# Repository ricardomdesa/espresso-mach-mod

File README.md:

# ☕ ESPresso

**Cafeteira Philco Espresso turbinada com um ESP32-C3:** controle PID de
temperatura da caldeira, modo vaporização, provisionamento Wi-Fi, API
REST/WebSocket e um app mobile (React + Capacitor) para configurar tudo.
Acompanha um **simulador em Go** que emula o firmware inteiro — dá pra
desenvolver o app sem encostar no hardware.

> ⚠️ **Projeto de hobby, mexe com rede elétrica AC.** SSR de 25 A, bomba
> vibratória e resistência de caldeira ligados na tomada. Se você não sabe
> isolar o lado AC do lado DC com segurança, **não reproduza.** Sem garantia
> de nada.

---

## O que dá pra fazer

- **PID de temperatura** na caldeira via SSR (time-proportioning, janela de 1 s),
  com anti-windup, derivada sobre a medição e cadência de 200 ms.
- **Termopar tipo K real** (MAX6675, SPI) com calibração linear de offset/ganho.
- **Modo vaporização:** o PID passa a mirar um alvo de vapor editável
  (80–115 °C) sem gravar na NVS; ao desligar, o setpoint de café volta para 70 °C.
- **Relé "temperatura pronta"** (contato seco, com histerese) para puxar shot
  manualmente, sem depender do app.
- **Perfis de extração** (pré-infusão, rampa, declínio) com CRUD pelo app e
  persistência em NVS.
- **Provisionamento Wi-Fi** no padrão AP + STA — o AP `Philco-Setup` **nunca**
  abre sozinho, só com hold de 5 s no botão. Descoberta por mDNS (`philco.local`).
- **App mobile** (Android/iOS via Capacitor): dashboard ao vivo por WebSocket,
  ajuste de PID/setpoint, gráficos da extração, histórico local offline.
- **Simulador** que espelha byte a byte o contrato REST/WS do firmware, com
  modelo térmico + PID portados do C++, e uma tela web mostrando SSR, bomba e LEDs.

### Failsafes de segurança

| Camada | Ação |
|---|---|
| Teto de sobretemperatura (115 °C) | duty forçado a 0 %, independente do PID |
| Leitura do termopar parada > 10 s | duty forçado a 0 % (sensor aberto/congelado) |
| Modo AP no ar | aquecedor forçado desligado (o scan de Wi-Fi bloqueia o loop) |
| Fusível na linha AC | última camada, contra SSR travado ligado |

---

## Estrutura do repositório

```
.
├── src/ · include/ · platformio.ini   Firmware ESP32-C3 (Arduino / PlatformIO)
├── secrets.ini.example                Modelo do secrets.ini (código de pareamento)
├── app/                               App React + TypeScript + Vite + Capacitor
├── simulator/                         Servidor Go que emula o ESP32 (REST + WS + web)
├── docs/                              Arquitetura, épicos, SDDs, calibração do PID
└── pinout2-1500.png                   Diagrama de pinagem
```

O firmware é dividido em módulos: `sensors/` (termopar, calibração, fakes),
`control/` (PID, saída do aquecedor), `net/` (Wi-Fi provisioner, servidor da API),
`config/` (NVS), `input/` (botão), `model/` (modelo de dados compartilhado).

---

## Hardware

| Bloco | Peça |
|---|---|
| MCU | ESP32-C3 Super Mini |
| Temperatura | Termopar tipo K + módulo MAX6675 (SPI) |
| Aquecimento | SSR AC 25 A acionado por driver TIP120, resistência original da caldeira |
| Bomba | Bomba vibratória Ulka original + módulo de relé (liga/desliga) |
| Sinalização | LED de iluminação + LED azul onboard |

### Pinagem (ESP32-C3)

| GPIO | Função |
|---|---|
| `3` | Botão tátil — clique: liga/desliga LED de luz · hold 5 s: sobe o AP de config |
| `20` | LED de iluminação (ativo HIGH) |
| `8` | LED azul onboard — pisca em modo setup (ativo LOW) |
| `5` / `6` / `7` | MAX6675 — SCK / SO(MISO) / CS |
| `10` | Base do driver TIP120 do SSR de aquecimento (ativo HIGH) |
| `0` | Sinal do relé da bomba (módulo active-low) |
| `1` | Sinal do relé "temperatura pronta" (contato seco, active-low) |

Detalhes de cada pino (motivo da escolha, strapping pins, estágio driver do SSR)
estão comentados em [`include/pinos.h`](include/pinos.h). Diagrama completo em
[`pinout2-1500.png`](pinout2-1500.png).

---

## Como rodar

### Firmware

Precisa de [PlatformIO](https://platformio.org/).

**Antes do primeiro build**, crie o `secrets.ini` com o código de pareamento da
sua máquina. Ele não é versionado — quem tem o código comanda a máquina (bomba,
setpoint, extração), então não pode viver num repositório público:

```sh
cp secrets.ini.example secrets.ini
openssl rand -hex 6                        # gere um código e ponha em auth_key
```

Sem esse arquivo o build falha de propósito. Anote o código numa etiqueta na
máquina: é ele que o app pede uma vez, no pareamento. Ele também sai no Serial
no boot. Trocar o código exige regravar o firmware e parear o app de novo.

```sh
pio run                                    # compila (env: esp32-c3-super-mini)
pio run -t upload && pio device monitor    # grava e abre o monitor serial (115200)
```

Sem credencial de Wi-Fi salva a máquina fica **offline** e o controle de
temperatura funciona standalone. Hold de 5 s no botão sobe o AP `Philco-Setup`
(IP `192.168.4.1`) para o app fazer o provisionamento.

Ambientes extras de bancada: `pio run -e wifi-ap-test`, `pio run -e wifi-sta-test`.

### App

Precisa de Node.js 18+.

```sh
cd app
npm install
npm run dev                # dev server no browser

npm run build              # build de produção
npx cap sync android       # sincroniza com o projeto nativo
npx cap open android       # abre no Android Studio (idem ios)
```

O app acha a máquina por mDNS (`philco.local`) com fallback para varredura de
subnet, ou por endereço manual (`host:porta`). Histórico de extrações fica local
via `@capacitor/preferences`.

### Simulador

Precisa de Go 1.21+ ou Docker.

```sh
cd simulator
docker compose up --build          # http://localhost:8080  (tela web em /)
# ou:
go run .                           # go run . -port 9000 -no-auth
```

No emulador Android, aponte o app para `10.0.2.2:8080` (endereço manual — a
auto-descoberta não alcança o host). Detalhes e todos os endpoints `/sim/*` de
controle da simulação em [`simulator/README.md`](simulator/README.md).

---

## API

`GET /ws` faz o streaming de leituras a cada 100 ms e emite eventos
(`extraction_started`, `extraction_stopped`, `error`). Rotas que mudam estado
exigem o header `X-Auth-Token` com o código de pareamento (dispensado só no
`provision` em modo AP); CORS liberado, `OPTIONS` responde 204. As rotas de
leitura são públicas: dá para ver as leituras sem código, mas não comandar.

| Método | Rota | O quê |
|---|---|---|
| `GET` | `/api/status` | snapshot completo (temp, pressão, setpoints, PID, flags, IP) |
| `GET` | `/api/auth/check` | valida o código de pareamento — 204 se vale, 401 se não |
| `PUT` | `/api/setpoint/temp` · `/api/setpoint/pressure` | alvos de temperatura / pressão |
| `PUT` | `/api/pid` | ganhos `{kp, ki, kd}` |
| `PUT` | `/api/led` · `/api/pump` · `/api/steam` | LED, bomba, modo vaporização |
| `POST` | `/api/extraction/start` · `/api/extraction/stop` | ciclo de extração + cronômetro |
| `GET` `POST` | `/api/profiles` | listar / criar perfil |
| `PUT` `DELETE` | `/api/profiles/{id}` | editar / remover perfil |
| `PUT` | `/api/profiles/active` | define o perfil ativo `{id}` |
| `GET` | `/api/wifi/scan` | redes visíveis (só em modo AP) |
| `POST` | `/api/wifi/provision` · `/api/wifi/forget` | salvar / esquecer credencial |
| `POST` | `/api/factory-reset` | limpa a NVS |

Contrato completo em [`src/net/ApiServer.cpp`](src/net/ApiServer.cpp) e
[`docs/sdd/006-api-rest-websocket.md`](docs/sdd/006-api-rest-websocket.md).

---

## Documentação

| Arquivo | Conteúdo |
|---|---|
| [`ARCHITECTURE.md`](ARCHITECTURE.md) | visão geral, BOM, divisão de responsabilidades, fluxo de provisionamento |
| [`docs/EPICS.md`](docs/EPICS.md) | roadmap por épicos, cada um com um SDD |
| [`docs/sdd/`](docs/sdd/) | design docs: OLED, sensor, PID, integração, Wi-Fi, API, app |
| [`docs/pid-calibracao.md`](docs/pid-calibracao.md) | log e método da calibração de Kp/Ki/Kd em bancada |

### Roadmap

| # | Épico | Status |
|---|---|---|
| 1 | Scaffold + modelo de dados + botão + cronômetro | ✅ |
| 2 | Sensor de temperatura (MAX6675 + calibração) | ✅ |
| 3 | Controle PID de temperatura + SSR | ✅ |
| 4 | Integração MVP + calibração no hardware | 🔧 em bancada |
| 5 | Wi-Fi + provisionamento (AP/STA, mDNS) | ✅ |
| 6 | API REST/WebSocket + persistência NVS | ✅ |
| 7 | App Android (React + Capacitor) | ✅ |
| — | Sensor de pressão real, balança (dose:yield), OTA | 📋 futuro |

O sensor de pressão ainda é `SensorFake` — o hardware é Fase 2. O OLED local foi
removido do projeto (queimou); toda a UI vive no app.

---

## Licença

A definir. Enquanto isso: use por sua conta e risco, sem garantia.

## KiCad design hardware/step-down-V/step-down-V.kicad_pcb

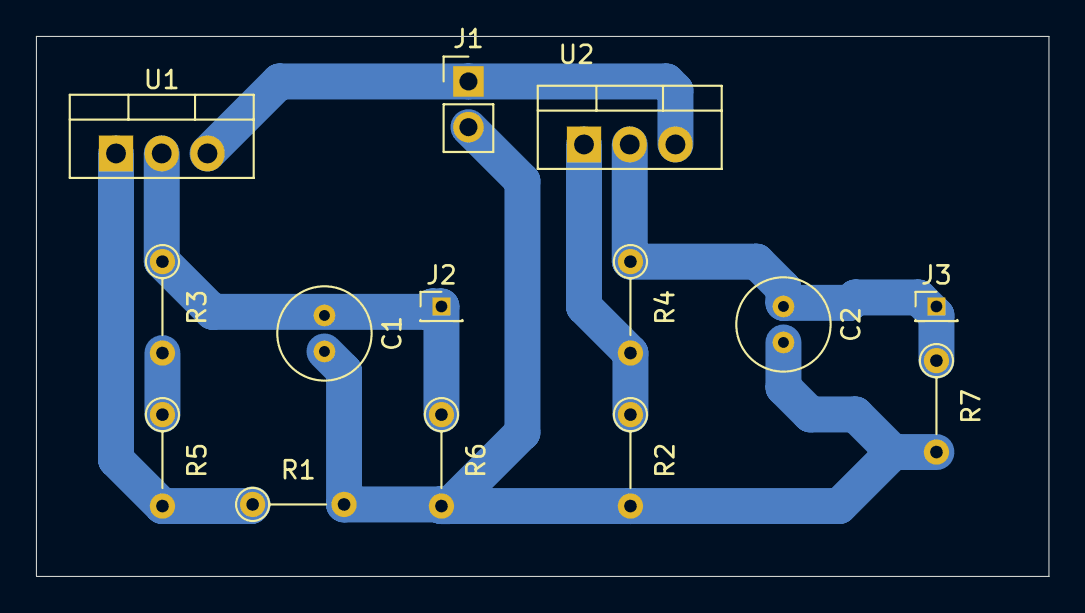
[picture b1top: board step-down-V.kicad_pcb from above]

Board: 2 copper layers, 56.2 x 30.0 mm, 14 parts (0 on the bottom side), 7 nets.

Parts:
C1, C2: C_Polarized; C_Radial_D5.0mm_H5.0mm_P2.00mm
J1: Vin 12V; PinHeader_1x02_P2.54mm_Vertical
J2, J3: Conn_01x01_Socket; PinHeader_1x01_P1.27mm_Vertical
R1: 470; R_Axial_DIN0204_L3.6mm_D1.6mm_P5.08mm_Vertical
R2: 330; R_Axial_DIN0204_L3.6mm_D1.6mm_P5.08mm_Vertical
R3: 120; R_Axial_DIN0204_L3.6mm_D1.6mm_P5.08mm_Vertical
R4: 260; R_Axial_DIN0204_L3.6mm_D1.6mm_P5.08mm_Vertical
R5: 20; R_Axial_DIN0204_L3.6mm_D1.6mm_P5.08mm_Vertical
R6, R7: 1K; R_Axial_DIN0204_L3.6mm_D1.6mm_P5.08mm_Vertical
U1, U2: LM317_TO-220; TO-220-3_Vertical

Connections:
GND: C1.2, C2.2, J1.2, R1.2, R2.2, R6.2, R7.2
unnamed: J1.1, U1.3 (VI), U2.3 (VI)
unnamed: C1.1, J2.1 (Pin_1_1), R3.1, R6.1, U1.2 (VO)
unnamed: C2.1, J3.1 (Pin_1_1), R4.1, R7.1, U2.2 (VO)
unnamed: R3.2, R5.1
unnamed: R1.1, R5.2, U1.1 (ADJ)
unnamed: R2.1, R4.2, U2.1 (ADJ)

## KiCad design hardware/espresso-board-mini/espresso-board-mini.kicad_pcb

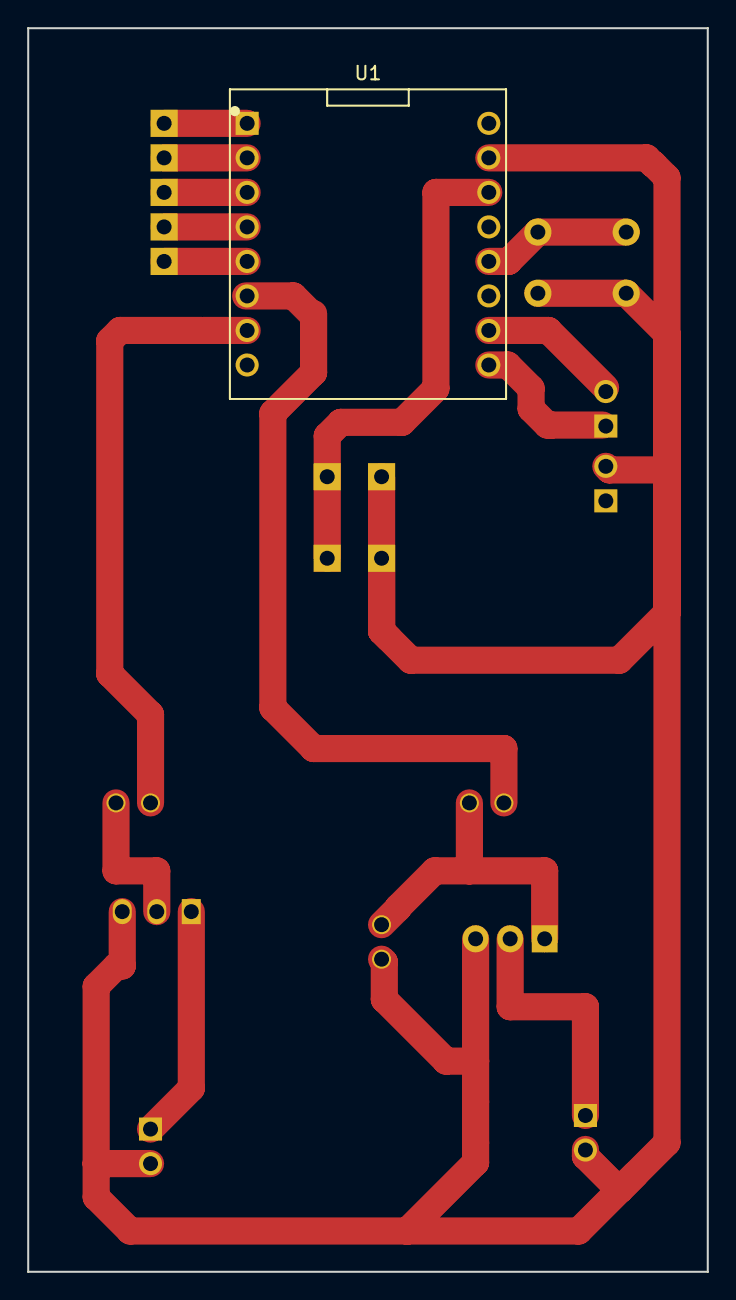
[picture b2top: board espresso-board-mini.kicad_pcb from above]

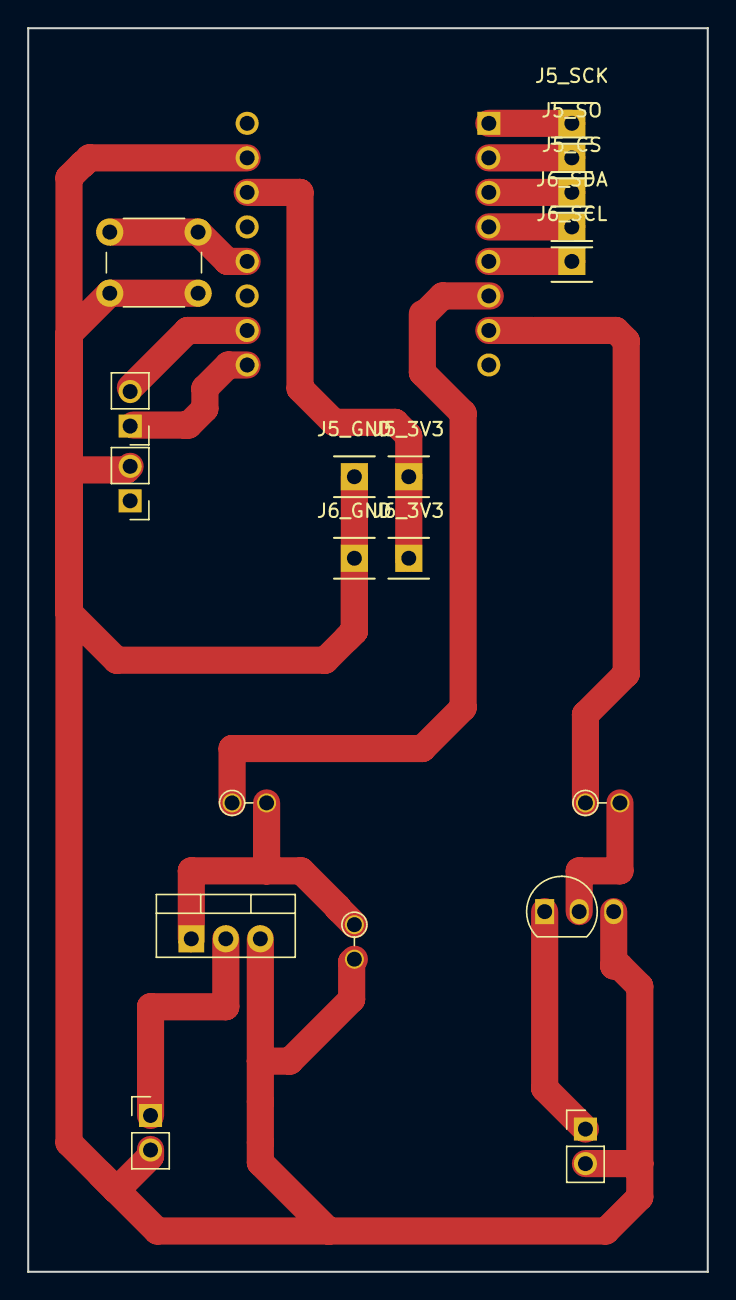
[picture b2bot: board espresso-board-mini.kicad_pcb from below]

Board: 2 copper layers, 50.0 x 91.5 mm, 10 parts (9 on the bottom side), 7 nets.

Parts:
J5_3V3: J_THERMO_3V3
J5_CS: THERMO_CS
J5_GND: J_THERMO_GND
J5_SCK: THERMO_SCK
J5_SO: THERMO_SO
J6_3V3: J_OLED_3V3
J6_GND: J_OLED_GND
J6_SCL: OLED_SCL
J6_SDA: OLED_SDA
U1: ESP32C3_SuperMini; ESP32C3_SuperMini_2x8_P2.54mm

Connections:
+3V3: J5_3V3.1, J6_3V3.1, U1.3 (3V3)
GND: J5_GND.1, J6_GND.1, U1.2 (GND)
OLED_SCL: J6_SCL.1, U1.13 (GPIO9)
OLED_SDA: J6_SDA.1, U1.12 (GPIO8)
THERMO_CS: J5_CS.1, U1.11 (GPIO7)
THERMO_SCK: J5_SCK.1, U1.9 (GPIO5)
THERMO_SO: J5_SO.1, U1.10 (GPIO6)

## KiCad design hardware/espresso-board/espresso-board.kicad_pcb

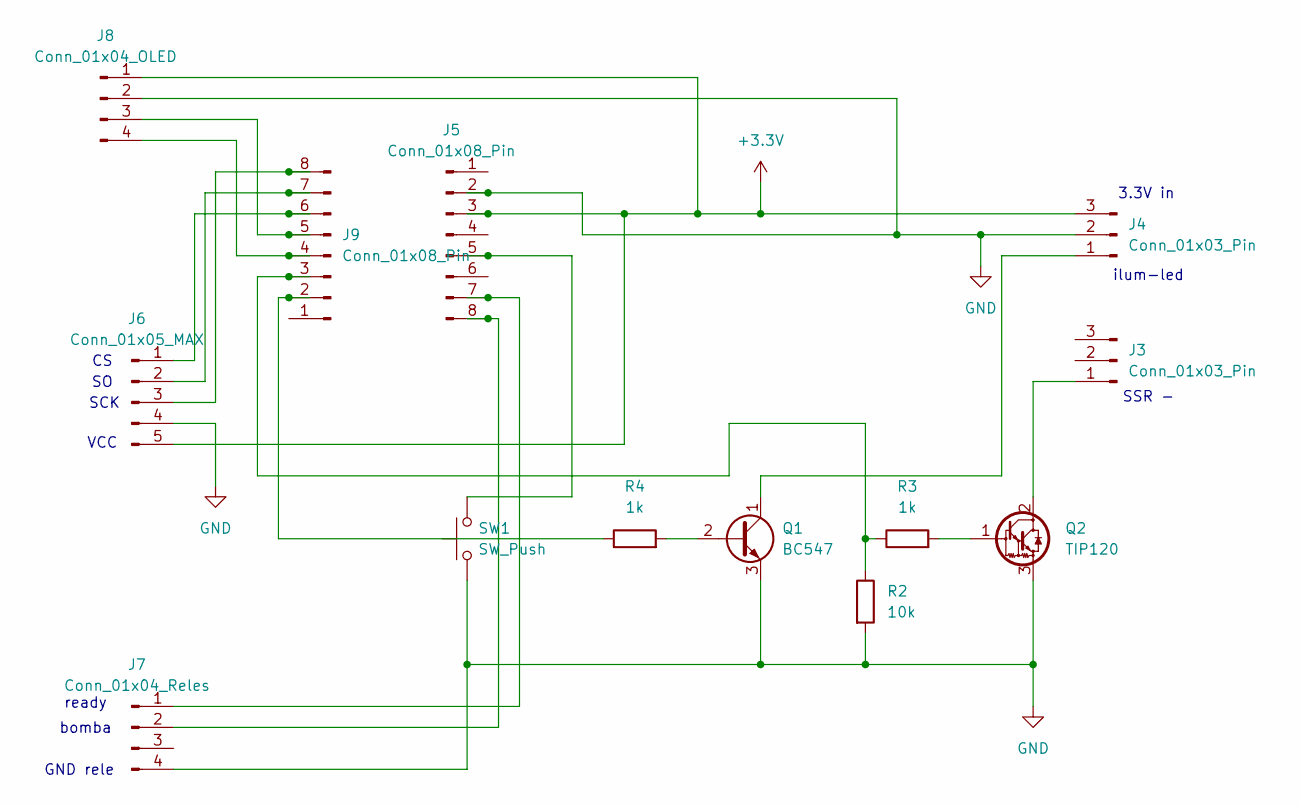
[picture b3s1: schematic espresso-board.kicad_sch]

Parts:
J3, J4: Conn_01x03_Pin; PinHeader_1x03_P2.54mm_Vertical
J5, J9: Conn_01x08_Pin; PinHeader_1x08_P2.54mm_Vertical
J6: Conn_01x05_MAX; PinHeader_1x05_P2.54mm_Vertical
J7: Conn_01x04_Reles; PinSocket_1x04_P2.54mm_Vertical
J8: Conn_01x04_OLED; PinSocket_1x04_P2.54mm_Vertical
Q1: BC547; TO-92_Inline
Q2: TIP120; TO-220-3_Vertical
R2: 10k; R_Axial_DIN0204_L3.6mm_D1.6mm_P2.54mm_Vertical
R3, R4: 1k; R_Axial_DIN0204_L3.6mm_D1.6mm_P2.54mm_Vertical
SW1: SW_Push; SW_PUSH_6mm

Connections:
+3.3V: J4.3, J5.3, J6.5, J8.1
GND: J4.2, J5.2, J6.4, J7.4, J8.2, Q1.3 (E), Q2.3 (E), R2.2, SW1.1
unnamed: J3.1 (Pin_1_1), Q2.2 (C)
unnamed: J4.1, Q1.1 (C)
unnamed: J5.5, SW1.2
unnamed: J5.7, J7.1
unnamed: J5.8, J7.2
unnamed: J6.1, J9.6
unnamed: J6.2, J9.7
unnamed: J6.3, J9.8
unnamed: J8.3, J9.5
unnamed: J8.4, J9.4
unnamed: J9.2, R4.1
unnamed: J9.3, R2.1, R3.1
unnamed: Q1.2 (B), R4.2
unnamed: Q2.1 (B), R3.2

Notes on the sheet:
ready
GND rele
SSR -
VCC
bomba
3.3V in
ilum-led
SCK

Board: 2 copper layers, 13 parts (1 on the bottom side), 16 nets, no tracks yet.

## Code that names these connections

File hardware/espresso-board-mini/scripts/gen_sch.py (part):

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from kiutils.items.common import Stroke, Fill

LEFT_PINS = ["5V", "GND", "3V3", "GPIO4", "GPIO3", "GPIO2", "GPIO1", "GPIO0"]
RIGHT_PINS = ["GPIO5", "GPIO6", "GPIO7", "GPIO8", "GPIO9", "GPIO10", "GPIO20", "GPIO21"]
POWER_NAMES = {"5V", "GND", "3V3"}

def make_effects(size=1.27):
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stub_label("U1", 8, -7.62, 0, "PUMP_GPIO0")                 # GPIO0 -> pump relay

# right column (pins 9-16)
stub_label("U1", 9, 7.62, 0, "THERMO_SCK")                  # GPIO5
stub_label("U1", 10, 7.62, 0, "THERMO_SO")                  # GPIO6
stub_label("U1", 11, 7.62, 0, "THERMO_CS")                  # GPIO7
stub_label("U1", 12, 7.62, 0, "OLED_SDA")                   # GPIO8
stub_label("U1", 13, 7.62, 0, "OLED_SCL")                   # GPIO9
stub_label("U1", 14, 7.62, 0, "SSR_ACT_GPIO10")             # GPIO10
stub_label("U1", 15, 7.62, 0, "LED_ACT_GPIO20")             # GPIO20
no_connect("U1", 16)                                        # GPIO21 spare
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add_symbol("Connector:Conn_01x05_Pin", "J5", "J_THERMO_MAX6675", P(99.06, 175.26))
stub_power("J5", 1, -6.35, 0, "power:GND", "GND")
stub_power("J5", 2, -6.35, 0, "power:+3.3V", "+3.3V")
stub_label("J5", 3, -6.35, 0, "THERMO_SCK")
stub_label("J5", 4, -6.35, 0, "THERMO_CS")
stub_label("J5", 5, -6.35, 0, "THERMO_SO")
text_note((91.44, 168.91), "J5: 1=GND 2=3V3 3=SCK 4=CS 5=SO (MAX6675)")

# ---- OLED I2C connector (4p: GND, +3V3, SDA, SCL) ----
add_symbol("Connector:Conn_01x04_Pin", "J6", "J_OLED_I2C", P(129.54, 175.26))
stub_power("J6", 1, 6.35, 0, "power:GND", "GND")
stub_power("J6", 2, 6.35, 0, "power:+3.3V", "+3.3V")
stub_label("J6", 3, 6.35, 0, "OLED_SDA")
stub_label("J6", 4, 6.35, 0, "OLED_SCL")
text_note((132.08, 168.91), "J6: 1=GND 2=3V3 3=SDA(GPIO8) 4=SCL(GPIO9)")

# ---- PWR_FLAG markers so ERC knows GND/+3V3 nets have a source (module's own supply/USB) ----
add_symbol_raw = None  # placeholder not used
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wire((184.15, 60.96), (184.15, 55.88))

text_note((80, 60), "espresso-board-mini -- ESP32-C3 Super Mini")
text_note((80, 63), "GPIO8/9 usados p/ I2C OLED -- status LED onboard nao usado no firmware")

# ---- sheet instances (required top-level section) ----
from kiutils.items.schitems import HierarchicalSheetInstance
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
